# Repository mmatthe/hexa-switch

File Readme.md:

# HexaSwitch - 6-Channel Switch for Tasmota

This project is a custom-designed printed circuit board (PCB) for a Tasmota-compatible IoT device based on the ESP32 microcontroller. It allows switching of **6 loads**, with each channel capable of handling up to **2 Amps**. The device contains a real-time clock such that the device can also run on an independent time base. 

I use it for switching on and off 12V valves for watering plants in the garden. It can also be used to switch relays and contactors to switch larger powers. 

---

## Features

- Link to [Schematic](schematic/schematic.pdf) and [BOM](schematic/bom/ibom.html)
- **ESP32-based** controller compatible with [Tasmota firmware](https://tasmota.github.io/)
- **6 independent load switching channels** (up to 2A per channel)
- **3 digital inputs**
- Supports power input from **5V to 24V**
- Optional **Real-Time Clock (RTC)** connector (not required for operation)
- Custom PCB designed using **KiCad**

---

## Hardware Details

- Power Supply: 5–24V DC input
- Switching: 6 channels, each capable of switching loads up to 2A
- Inputs: 3 digital inputs
- Microcontroller: ESP32
- Optional RTC interface for time-sensitive automation

---

## Usage

1. Assemble the PCB and connect loads to the output channels.
2. Flash the ESP32 with [Tasmota firmware](https://tasmota.github.io/).
3. Power the device with a DC supply between 5V and 24V.
4. Use Tasmota’s web interface or MQTT to control each channel independently.

---

## License

This project is released under the MIT License.

---

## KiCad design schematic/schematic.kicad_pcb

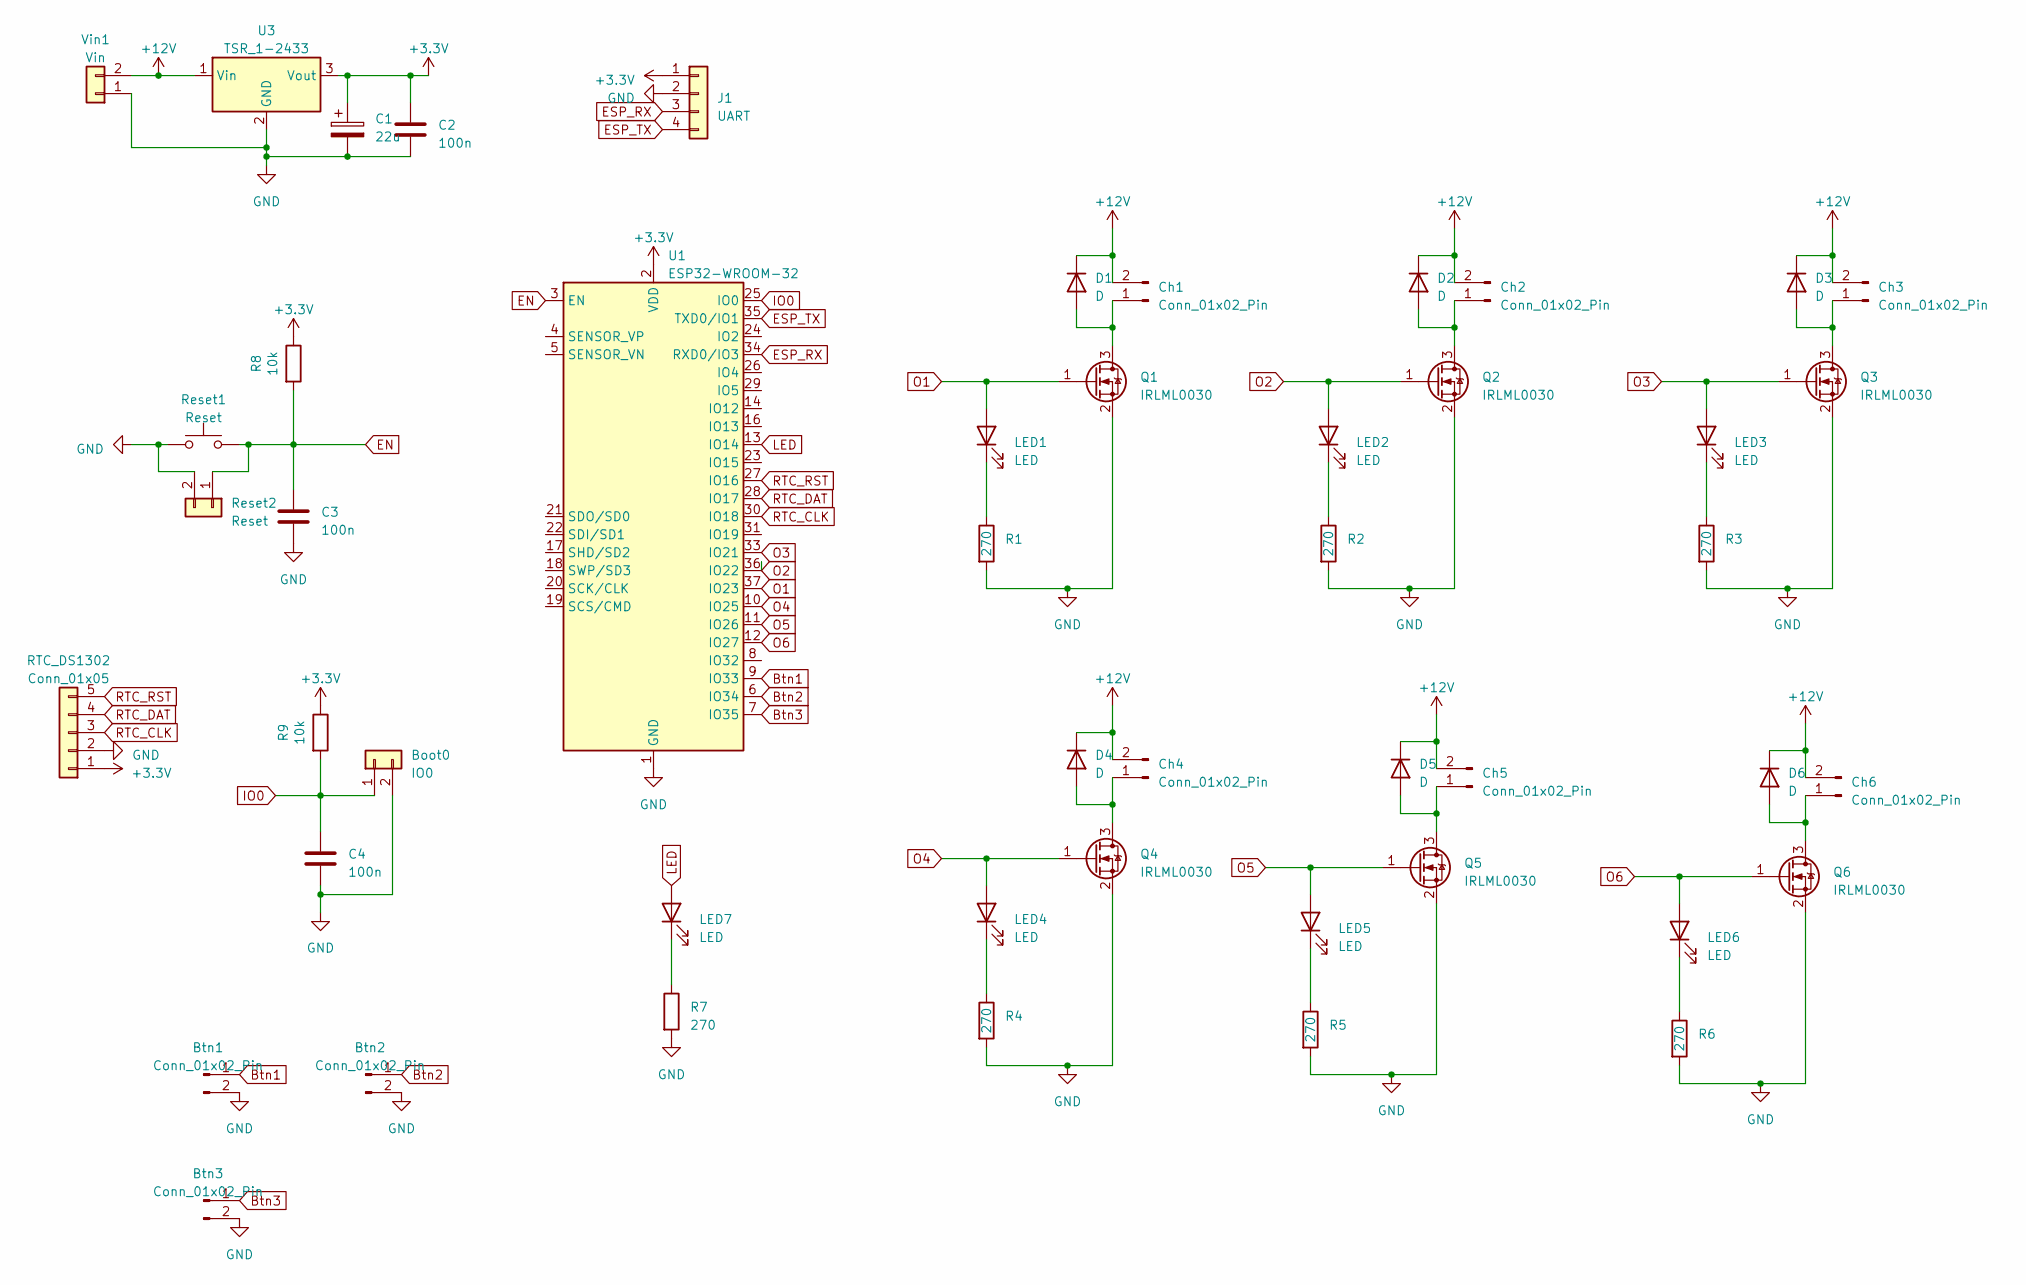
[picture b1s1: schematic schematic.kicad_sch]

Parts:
Boot0: IO0; PinHeader_1x02_P2.54mm_Vertical
Btn1, Btn2, Btn3: Conn_01x02_Pin; PinHeader_1x02_P2.54mm_Vertical
C1: 22u; CP_Radial_D5.0mm_P2.50mm
C2, C3, C4: 100n; C_0805_2012Metric
Ch1, Ch2, Ch3, Ch4, Ch5, Ch6: Conn_01x02_Pin; JST_XH_B2B-XH-AM_1x02_P2.50mm_Vertical
D1, D2, D3, D4, D5, D6: D; D_SOD-123
J1: UART; PinSocket_1x04_P2.54mm_Vertical
LED1, LED2, LED3, LED4, LED5, LED6, LED7: LED; LED_0805_2012Metric
Q1, Q2, Q3, Q4, Q5, Q6: IRLML0030; SOT-23
R1, R2, R3, R4, R5, R6, R7: 270; R_0805_2012Metric
R8, R9: 10k; R_0805_2012Metric
RTC_DS1302: Conn_01x05; PinSocket_1x05_P2.54mm_Vertical
Reset1: Reset; Reichelt 9315
Reset2: Reset; PinHeader_1x02_P2.54mm_Vertical
U1: ESP32-WROOM-32
U3: TSR_1-2433; Converter_DCDC_TRACO_TSR-1_THT
Vin1: Vin; JST_XH_B2B-XH-AM_1x02_P2.50mm_Vertical

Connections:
+3.3V: C1.1, C2.1, J1.1, R8.1, R9.1, RTC_DS1302.1, U1.2 (VDD), U3.3 (Vout)
+12V: Ch1.2, Ch2.2, Ch3.2, Ch4.2, Ch5.2, Ch6.2, D1.1 (K), D2.1 (K), D3.1 (K), D4.1 (K), D5.1 (K), D6.1 (K), U3.1 (Vin), Vin1.2
Btn1: Btn1.1, U1.9 (IO33)
Btn2: Btn2.1, U1.6 (IO34)
Btn3: Btn3.1, U1.7 (IO35)
EN: C3.1, R8.2, Reset1.2, Reset2.1, U1.3 (EN)
ESP_RX: J1.3, U1.34 (RXD0/IO3)
ESP_TX: J1.4, U1.35 (TXD0/IO1)
GND: Boot0.2, Btn1.2, Btn2.2, Btn3.2, C1.2, C2.2, C3.2, C4.2, J1.2, Q1.2 (S), Q2.2 (S), Q3.2 (S), Q4.2 (S), Q5.2 (S), Q6.2 (S), R1.2, R2.2, R3.2, R4.2, R5.2, R6.2, R7.2, RTC_DS1302.2, Reset1.1, Reset2.2, U1.1 (GND), U1.15 (GND), U1.38 (GND), U1.39 (GND), U3.2 (GND), Vin1.1
IO0: Boot0.1, C4.1, R9.2, U1.25 (IO0)
LED: LED7.2 (A), U1.13 (IO14)
unnamed: Ch1.1, D1.2 (A), Q1.3 (D)
unnamed: Ch2.1, D2.2 (A), Q2.3 (D)
unnamed: Ch3.1, D3.2 (A), Q3.3 (D)
unnamed: Ch4.1, D4.2 (A), Q4.3 (D)
unnamed: Ch5.1, D5.2 (A), Q5.3 (D)
unnamed: Ch6.1, D6.2 (A), Q6.3 (D)
unnamed: LED1.1 (K), R1.1
unnamed: LED2.1 (K), R2.1
unnamed: LED3.1 (K), R3.1
unnamed: LED4.1 (K), R4.1
unnamed: LED5.1 (K), R5.1
unnamed: LED6.1 (K), R6.1
unnamed: LED7.1 (K), R7.1
O1: LED1.2 (A), Q1.1 (G), U1.37 (IO23)
O2: LED2.2 (A), Q2.1 (G), U1.36 (IO22)
O3: LED3.2 (A), Q3.1 (G), U1.33 (IO21)
O4: LED4.2 (A), Q4.1 (G), U1.10 (IO25)
O5: LED5.2 (A), Q5.1 (G), U1.11 (IO26)
O6: LED6.2 (A), Q6.1 (G), U1.12 (IO27)
RTC_CLK: RTC_DS1302.3, U1.30 (IO18)
RTC_DAT: RTC_DS1302.4, U1.28 (IO17)
RTC_RST: RTC_DS1302.5, U1.27 (IO16)

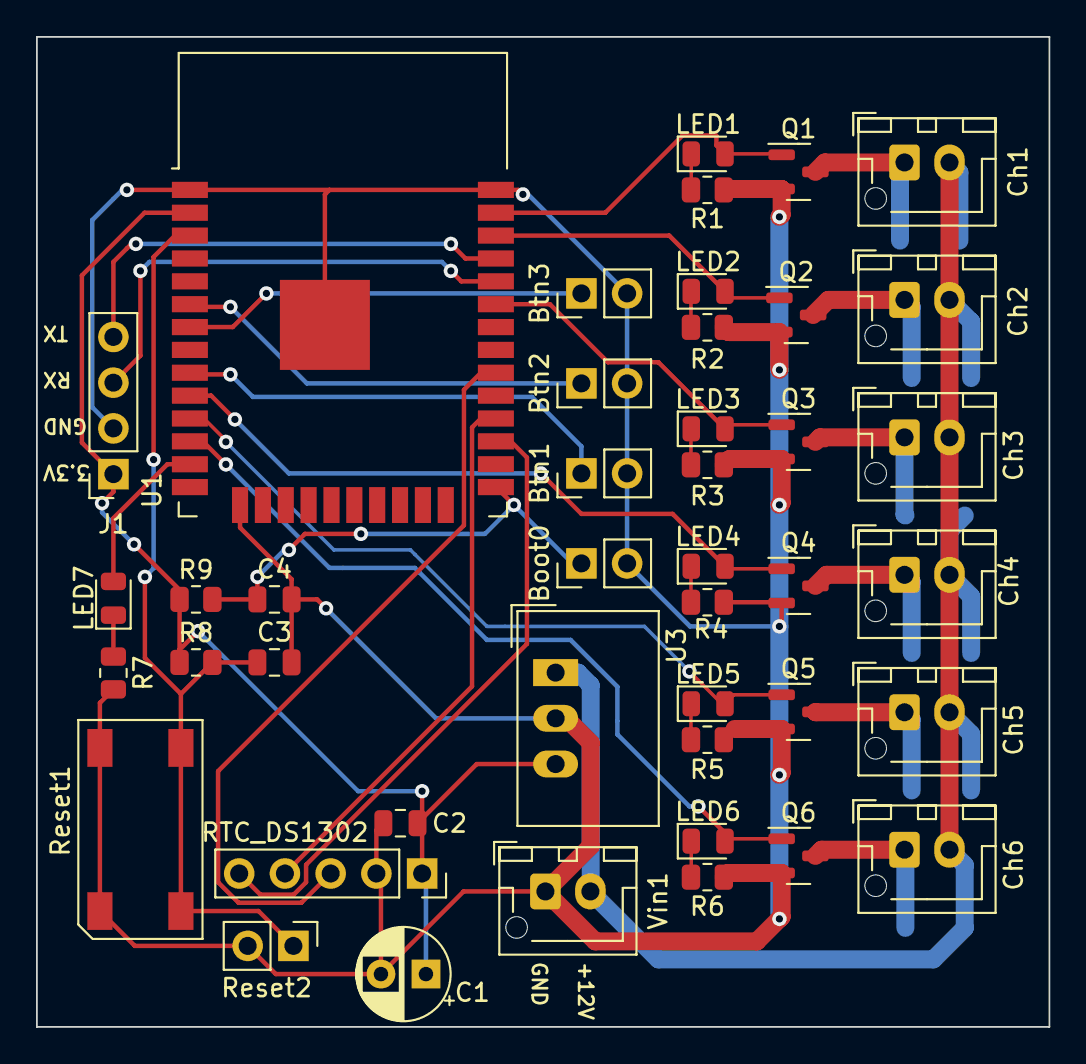
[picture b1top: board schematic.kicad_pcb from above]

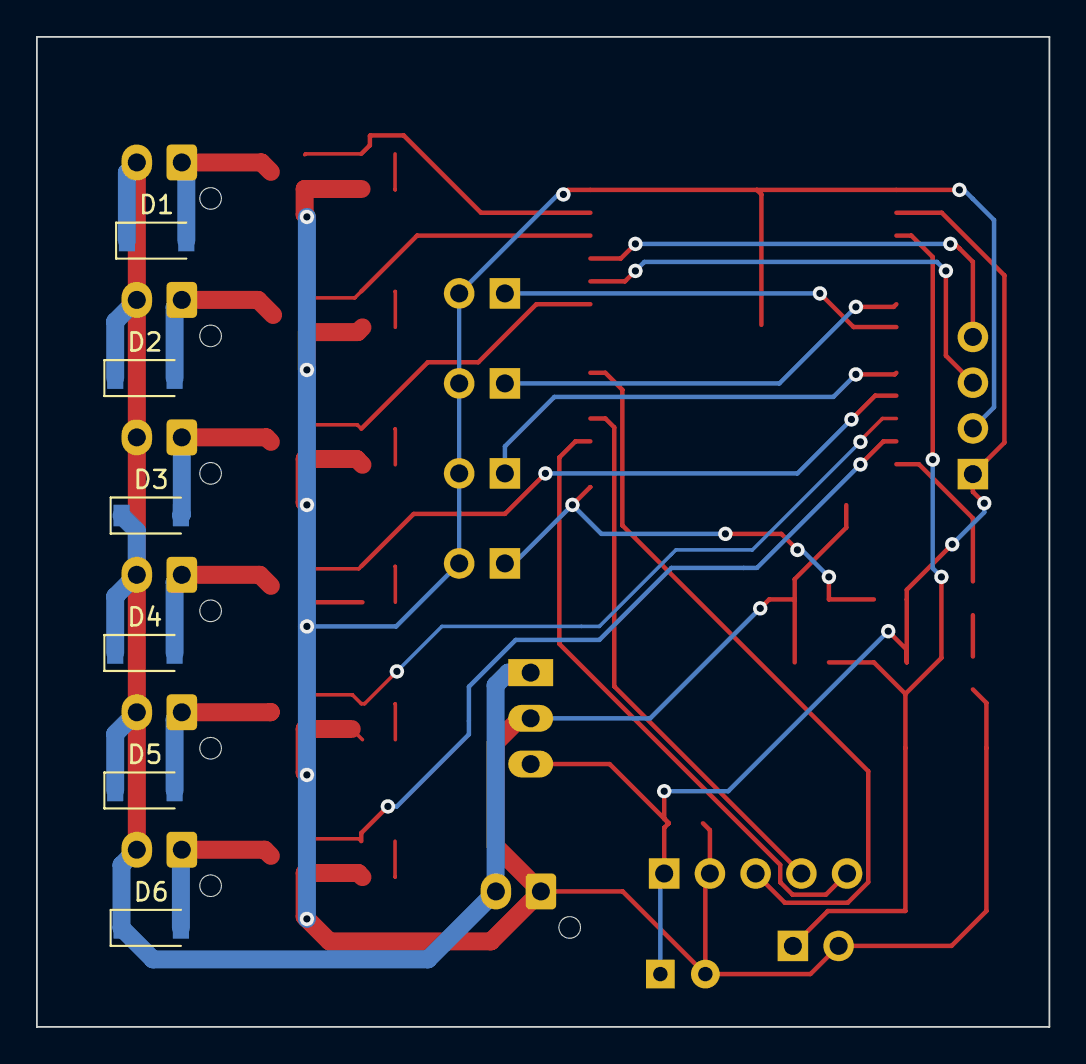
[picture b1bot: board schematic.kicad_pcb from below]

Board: 2 copper layers, 56.2 x 55.0 mm, 49 parts (6 on the bottom side), 33 nets.

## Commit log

2025-05-28 add readme and case
2025-05-28 add schematic
2025-05-28 add image
2025-05-28 update image
2025-05-28 add images
2025-05-28 add BOM
